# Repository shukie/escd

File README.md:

# escd-diodeless keyboard

The "escd-diodeless" keyboard is a thin split keyboard with 3x6 column staggered keys, 4 thumb keys, and one big escape key (46 keys total). There are no LEDs or diodes, only for CHERRY MX Low Profile switches and Elite-C controllers.

"escd" is pronounced as "escaped.”

## Design

## Directories

```text
├── doc
│   └── image
├── escd-diodeless
│   ├── firmware   ... The firmware.
│   ├── garbar     ... Garbar files For 3D printing.
│   ├── pcb        ... KiCad files for PCB.
│   └── plate      ... Inkscape files for acrylic plates.
├── keycap         ... FreeCad files for keycaps.
├── layout         ... "keyboard-layout-editor" file.
└── qmk-keyboards
    └── escd       ... The source of the firmware.
```

### Layout

### PCB

The PCB is designed reversible. The thickness is 1.6mm.

23 pins of the Elite-C controller are directly connected to switches. This is why the keyboard doesn’t need diodes.
Almost all Elite-C pins are used but a reset pin because it has a tiny reset button.

<https://deskthority.net/wiki/Elite-C#Version_4.0>

### Plates

The thickness of the acrylic plates is 2.0mm.

There are 4 types of acrylic plates. Top, bottom, and 2 little cover plates.
The bottom plates need an M2 tap work for sandwich PCB.

### Keycaps

There are 6 types of 1u (Center, CenterHome, Side, Corner, Thumb, ThumbHome) and 2 types of 1.5u (ESC, Space) keycaps designed for CHERRY MX Low Profile.

I recommend 3D printing by MJF PA11 without polishing and applying a matte clear coat on the top surface.

### Firmware

Use QMK Toolbox to install the firmware (`escd-diodeless/firmware/escd_diodeless_default.hex`) to Elite-C controllers.

`qmk-keyboards/escd` directory is for qmk_firmware. Symlink or copy the directory to the `qmk_firmware/keyboards` directory and modify [keymaps](qmk-keyboards/escd/diodeless/keymaps/default/keymap.c) if you want.

## Build guide

### Parts

- Elice-C controller x 2
- CHERRY MX Low Profile switches x 46
- TRRS jack x 2
- M2x6mm screw x 10
- M2x5mm screw x 6
- M2x3mm screw x 18
- M2x3mm spacer x 6
- M2x5mm spacer x 6
- Rubber foot x 8

- TRRS cable x 1
- Type-C USB cable x 1

### Special tool

- M2 tap

### Build steps

1. Cut the switch and TRRS jack pins so they don't protrude from the PCB.
  
2. Solder switches, TRRS jacks, and Elite-C controllers.
  
3. Install firmware and test the keyboard to make sure it works.  
  Connect the keyboard to a PC with a Type-C cable and install the firmware.  
  Connect both sides with a TRRS cable, and connect the left keyboard to the PC with the Type-C cable. Then test all keys on the keyboard.
4. Tap in the bottom plates.
  
5. Put the bottom plates and covers.
  
6. Put rubber feet.

## License

See the [LICENSE](LICENSE.txt) file for license rights and limitations (MIT).

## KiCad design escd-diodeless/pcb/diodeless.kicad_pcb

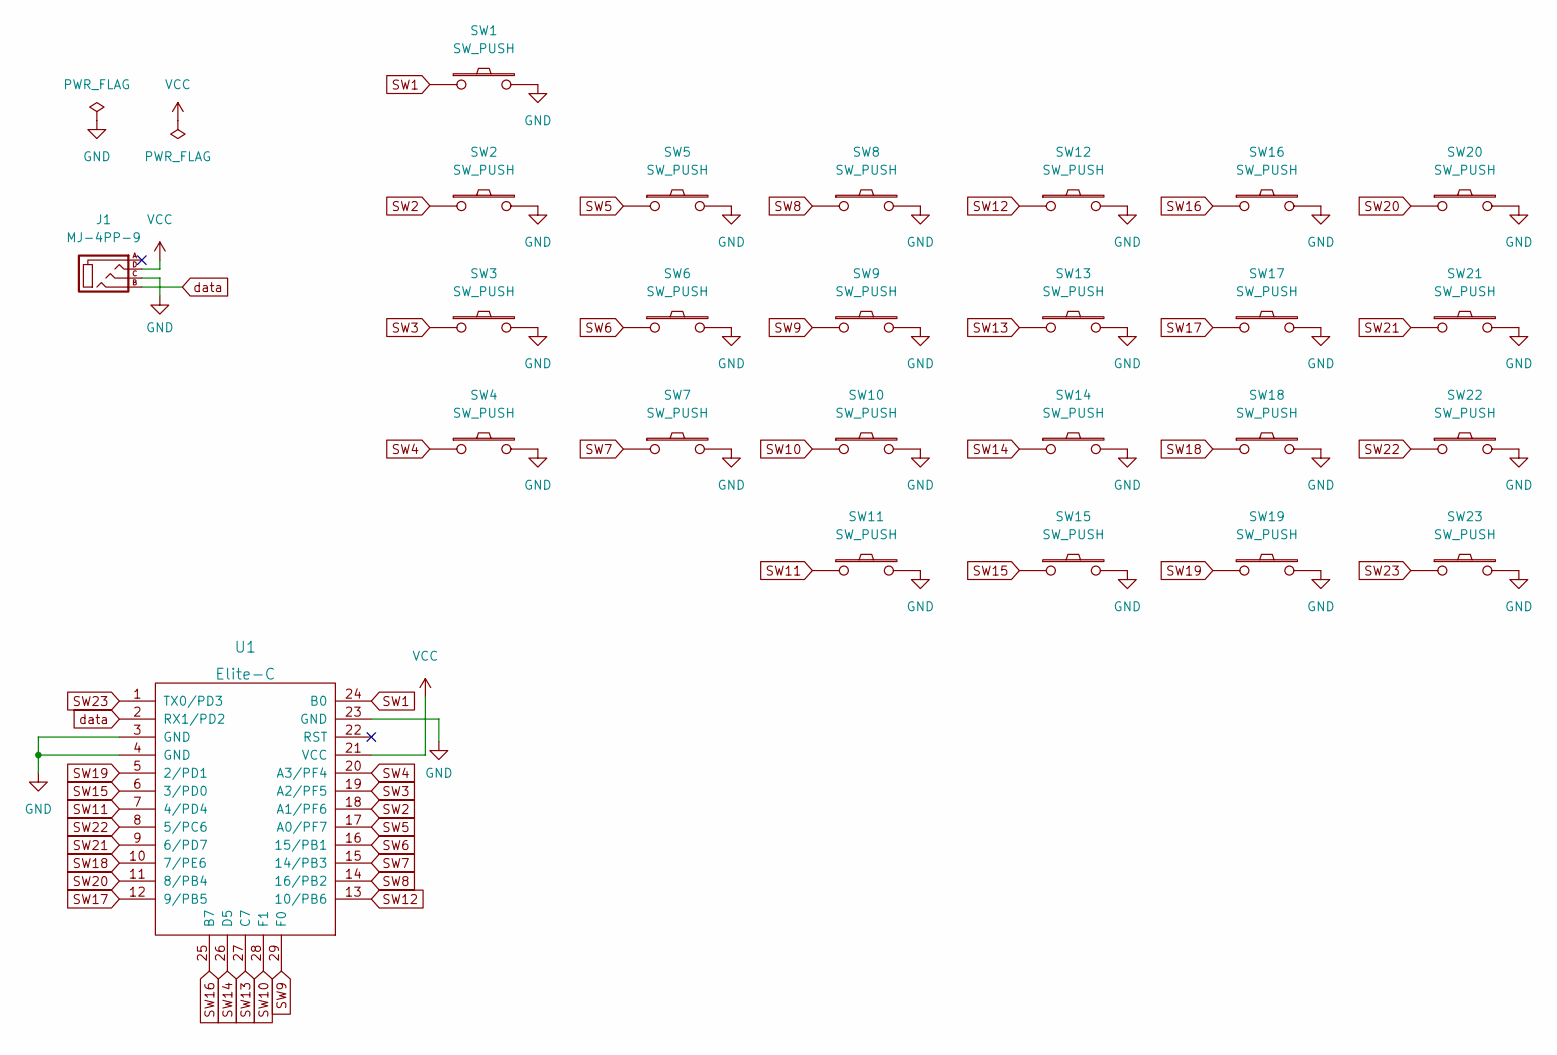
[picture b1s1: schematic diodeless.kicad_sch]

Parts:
J1: MJ-4PP-9
SW1: SW_PUSH; Cherry-MX-Low-Profile-u1.5
SW2, SW3, SW4, SW5, SW6, SW7, SW8, SW9, SW10, SW11, SW12, SW13, SW14, SW15, SW16, SW17, SW18, SW19, SW20, SW21, SW22: SW_PUSH; Cherry-MX-Low-Profile
SW23: SW_PUSH; Cherry-MX-Low-Profile-u1.5-vertical
U1: Elite-C; Elite-C-castellated-29pin

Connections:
GND: J1.C, SW1.2, SW2.2, SW3.2, SW4.2, SW5.2, SW6.2, SW7.2, SW8.2, SW9.2, SW10.2, SW11.2, SW12.2, SW13.2, SW14.2, SW15.2, SW16.2, SW17.2, SW18.2, SW19.2, SW20.2, SW21.2, SW22.2, SW23.2, U1.3 (GND), U1.4 (GND), U1.23 (GND)
SW1: SW1.1, U1.24 (B0)
SW2: SW2.1, U1.18 (A1/PF6)
SW3: SW3.1, U1.19 (A2/PF5)
SW4: SW4.1, U1.20 (A3/PF4)
SW5: SW5.1, U1.17 (A0/PF7)
SW6: SW6.1, U1.16 (15/PB1)
SW7: SW7.1, U1.15 (14/PB3)
SW8: SW8.1, U1.14 (16/PB2)
SW9: SW9.1, U1.29 (F0)
SW10: SW10.1, U1.28 (F1)
SW11: SW11.1, U1.7 (4/PD4)
SW12: SW12.1, U1.13 (10/PB6)
SW13: SW13.1, U1.27 (C7)
SW14: SW14.1, U1.26 (D5)
SW15: SW15.1, U1.6 (3/PD0)
SW16: SW16.1, U1.25 (B7)
SW17: SW17.1, U1.12 (9/PB5)
SW18: SW18.1, U1.10 (7/PE6)
SW19: SW19.1, U1.5 (2/PD1)
SW20: SW20.1, U1.11 (8/PB4)
SW21: SW21.1, U1.9 (6/PD7)
SW22: SW22.1, U1.8 (5/PC6)
SW23: SW23.1, U1.1 (TX0/PD3)
VCC: J1.D, U1.21 (VCC)
data: J1.B, U1.2 (RX1/PD2)

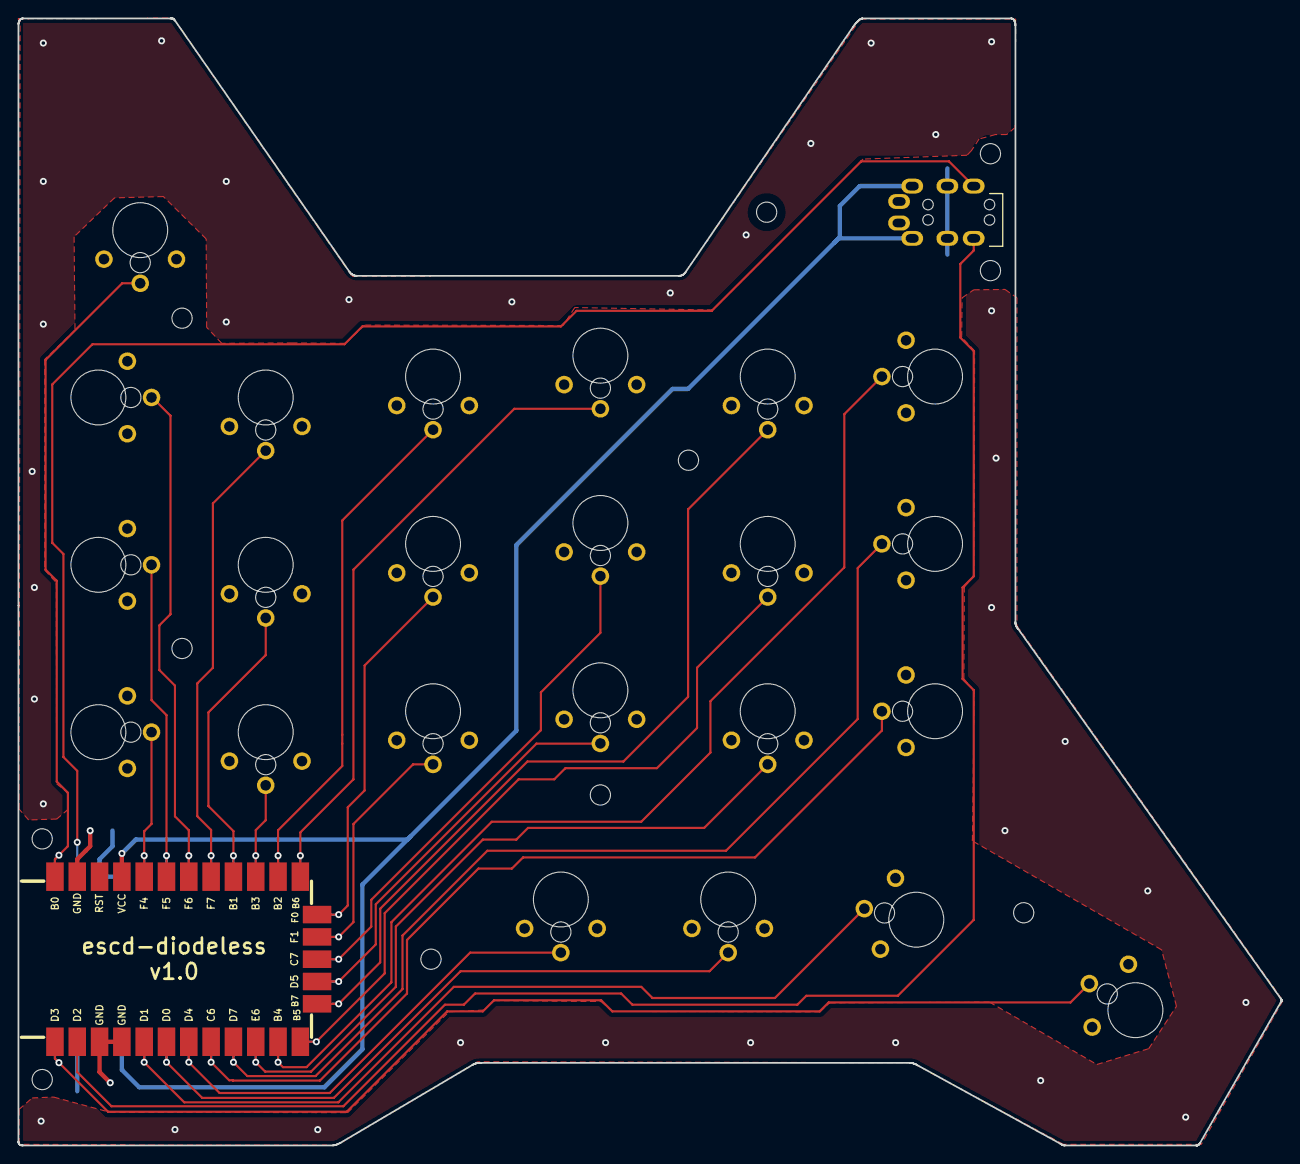
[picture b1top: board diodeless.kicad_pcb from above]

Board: 2 copper layers, 143.8 x 128.3 mm, 36 parts (0 on the bottom side), 26 nets.

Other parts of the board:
H1, H2, H3, H4, H5, H6, H7, H8, H9, H10, H11: Val**; M2_HOLE_WITH_CLEARANCE
